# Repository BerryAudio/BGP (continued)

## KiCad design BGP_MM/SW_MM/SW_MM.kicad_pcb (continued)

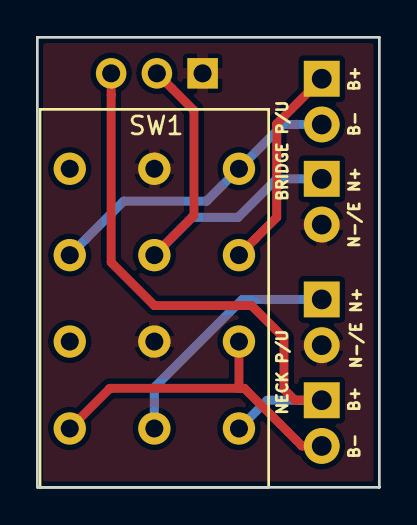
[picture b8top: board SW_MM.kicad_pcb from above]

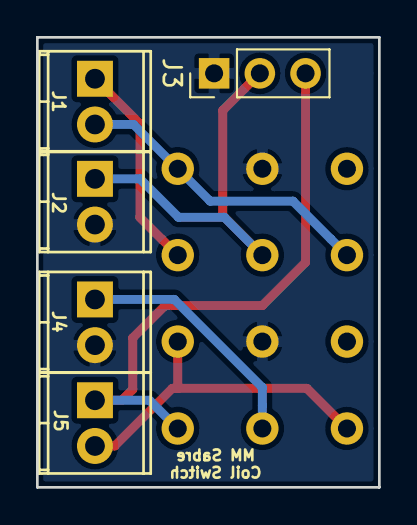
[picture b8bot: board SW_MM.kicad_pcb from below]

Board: 2 copper layers, 19.0 x 25.0 mm, 6 parts (5 on the bottom side), 7 nets.

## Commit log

2018-01-11 First haul
2018-01-11 Gerbers
    Mainly getting gerbers ready. Issue with pots overlapping other boards in silk screens - top and bottom.
2018-01-11 Fixups
2018-01-12 Pot fixups for silkscreen overlap
2018-01-12 Concentric pot fixups for 0_BT Stack and 1_HPF
2018-01-12 Concentric pot fixups for 1_BUF
2018-01-12 BOM for V1 BGP
2018-01-12 Further component refinement in V1
2018-01-12 Gerbers updated
2018-01-12 V_0 Updates for caps, gerbers updated
2018-01-13 some cleanup
2018-01-13 OPAMP MODEL CHANGED
2018-01-13 sim update
2018-01-14 V0 BUF and BT Edits
    V0 Buffer change from CRD to JFET CCS. BT stack changed to reflect +/- 9V changes.
2018-01-14 Slight changes to Port layer placement - gerbers done
2018-01-15 Some cleanup and gerbers updated to reflect this
2018-01-15 Changed Mid sweep
    200 - 2k Hz
2018-01-16 Error found/corrected in 1_VOL. Modified to use ALPS RK097 dual shaft, quad gang.
2018-01-16 Changed 1_HPF to use ALPHA 12mm pot.
2018-01-16 Reduced BT MID board sizes.
2018-01-17 New Filter deisgn - bug in previous
2018-01-17 f1 pcb complete
2018-01-17 F1 pcb trimmed
2018-01-17 F1 VOL Prot Diode
2018-01-18 F boards routed, various optimisations made
2018-01-18 Hand route F VOL board
2018-01-18 Add some missing files
2018-01-18 F VOL
    POT EARTH FIXUP
2018-01-18 Flipped boards so that they should be facing the right way
2018-01-19 Pot tinkering
2018-01-19 Updated F_VOL
    Using 10kB, 100kA pot with correct orientation, and pot correction for blend.
2018-01-22 New F0 Version
2018-01-22 F0 Buffer Board
    Buffer done. 30mm x 40mm, with optional outboard volume or concentric vol/blend. Output bypass EQ and straight to output possible.
2018-01-22 clranup
2018-01-23 Added BT and MID. Mid not layed out yet
2018-01-23 Deleted some sims
2018-01-24 F0 BUF is now 26x40
2018-01-24 F0 Mid Stack done
2018-01-24 LOG Sim Spreadsheet
2018-01-24 F0 VOL Board Added
2018-01-24 F0 prot diode added, bt changed to 26mm
2018-01-24 F0 - Volume Corrected
2018-01-24 Revert "F0 - Volume Corrected"
    This reverts commit ecfa2db017f63e3919b6c9b3f933c0864d41a2a5.
2018-01-25 Removed old boards, all F0 are now 26mm deep
2018-01-25 BT and MID pot gain ctrl reversed for proper action
2018-01-28 Started work on Discrete Version
2018-01-29 Working on JFET based amp, pots are an issue
2018-01-29 Sim Cleanup And POC
2018-01-29 Notes, and slight reorg
2018-01-30 Schematics done, pcb layout pending:
2018-01-30 Schematics done, pcb layout pending
2018-01-31 PCB Layout done
2018-01-31 PCB Layout cleanup
2018-01-31 Changed Term Blocks in BT stack to JST connector to BND
2018-01-31 Flipped BT to VOL connector on BT board to bottom side for better conn
2018-01-31 Changed POT, parallel VOL pot conn for offboard pot
2018-02-01 Some cleanup, and gain stage changes
2018-02-01 Slight buffer change
2018-02-01 Pots were out by a little, changed PCBs accordingly
2018-02-03 Changed Gain structure a bit
2018-02-03 Cleanup
2018-02-04 Value and gain structure tweak
2018-02-04 Sim Update - SF Load update
2018-02-05 Some Changes
2018-02-07 F0 Final
2018-02-08 Some fixes and refinement
2018-02-08 J Amp changed for imrpoved distortion performance
2018-02-09 J BT Cap changes
2018-02-09 J BT Caps to film
2018-02-09 Various - BOM complete
2018-02-11 Tone cap changed to female pin strip header for 0.047uF and 0.1uF
2018-02-12 J BT Pot wired incorrectly
2018-02-12 J Cap footprint changes
2018-02-12 Various
2018-02-13 J BT Changes from SMD film caps to THT
2018-02-13 minor
2018-02-14 J BT Track Changes
2018-02-15 Cap change
2018-02-15 Misc
2018-02-17 Mid Buff
2018-02-18 Change some caps to TH, updated BOM - need to recreate
2018-02-18 Some extras
2018-02-19 Tone pot 20k
2018-02-19 J BT ... not much
2018-02-28 Add JFET Vgs(off) test board)
2018-02-28 Old Gerbers removed
2018-02-28 Mods and gerbers done
2018-02-28 Clean up some images
2018-03-01 Changed some layout for pot overlap
2018-03-03 convert drl to txt files
2018-04-08 Added SVF sim file
2018-04-08 Noise
2018-04-11 Jfet buffering added to SVF output control
2018-04-11 F1 updates to reverse pots
2018-04-11 add ALPS pot and jfet lib into F1
2018-04-13 HPF Done
2018-04-25 J0 Tone Pot Fixup
2018-04-25 J0 Tone Control Fixup
2018-04-26 Revert some changes
2018-04-26 Final J0 tone pot fixes
2018-04-26 J0 VOL board modded for all CONN on bottom side
2018-04-26 J0 VOL removed VOL CONN, slight rerouting
2018-04-27 Normalising Schematics part list for J0
2018-04-29 J0 prepped for board run with blend board
2018-04-29 J0 - Panelisation
2018-04-30 BOM complete and changes made to PCBs for cap changes
2018-04-30 Part no updates
2018-04-30 Gerbers fixed - ready to go
2018-04-30 Ready to go
    Reverted J0_BND to include P/U inputs
2018-05-02 Stuff
2018-05-03 F0 Mid Stack fixed
2018-05-03 BOM Update
2018-05-03 F0 BT stack changed slightly
2018-05-05 F0 Pot Wiring reversed after testing
2018-05-09 Refined Buffer F0
2018-05-09 F0 Conn changes
2018-05-09 F0 - Boost only bass
2018-05-10 F0 - Boost only - boost/cut bypass
2018-05-10 Slight changes
2018-05-10 BOM - Some caps cheaper at RS
2018-05-10 F0 BT Layout
2018-05-11 Some changes to names
2018-05-11 F0 - Fixed Mid Stack, BT, BUF
2018-05-11 F0 BUF changed rotation
2018-05-11 Tone Pot connector and output routing added
2018-05-12 F0 Vol/Vol spec LOG pots
2018-05-13 F0 - BUF JFET bypass caps at i/p
2018-05-15 Single Board J0 - J1
2018-05-18 Adding MM
2018-05-20 Adding Datasheets
2018-05-22 Updates MM
2018-05-22 MM Update
2018-05-23 PCB Started
2018-05-24 MM Finished board layouts
2018-05-24 MM T ctrl reversed for proper operation
2018-05-24 Switch schematics
2018-05-25 MM Routing complete
2018-05-25 MM Tweaks
2018-05-25 MM BT Tweak for weak gnd and vref to IC1
2018-05-26 MM - Board changes
2018-05-28 tweaks
2018-06-02 MM Connector Verification
2018-06-02 Board Labels
2018-06-04 MM Switches and BOM
2018-06-04 MM Gerbers, BASS pot fixup
2018-06-05 MM Gerbers Finished, Mid Stack Ammended J0
2018-06-05 F0 Gerbers
2018-06-05 MM Gerber update
2018-06-05 MM Switch Config Changed
2018-06-05 MM Gerbers
2018-06-05 MM Zip
2018-06-06 BT Bright Cap/Res changed
2018-06-07 MM Switch
2018-06-08 MM Refactoring
2018-06-12 F0 Tone CTRL
2018-06-13 Minor tweaks for MM/F0 - gerbers ready to go out
2018-06-13 MM PCB comments
2018-06-13 BOM Work prior to sending Gerbers
2018-06-13 BOM Updates
2018-06-14 BOM Work complete
2018-06-14 F0 Gerbers redone after BOM changes
2018-06-14 Minor BOM changes
2018-06-14 Gerbers altered and sent
2018-06-14 Remove Basket from BOM
2018-08-26 J0 - BT Connectors changed to pin headers
2018-08-27 J0 - Modified all files to remove JST connectors
2018-08-27 J0 - Changed BT Caps to larger/Cheaper form factor
2018-08-28 J0 - Gerbers changed
2018-08-28 J0 - BND
2018-08-28 J0 BT C to SMT
